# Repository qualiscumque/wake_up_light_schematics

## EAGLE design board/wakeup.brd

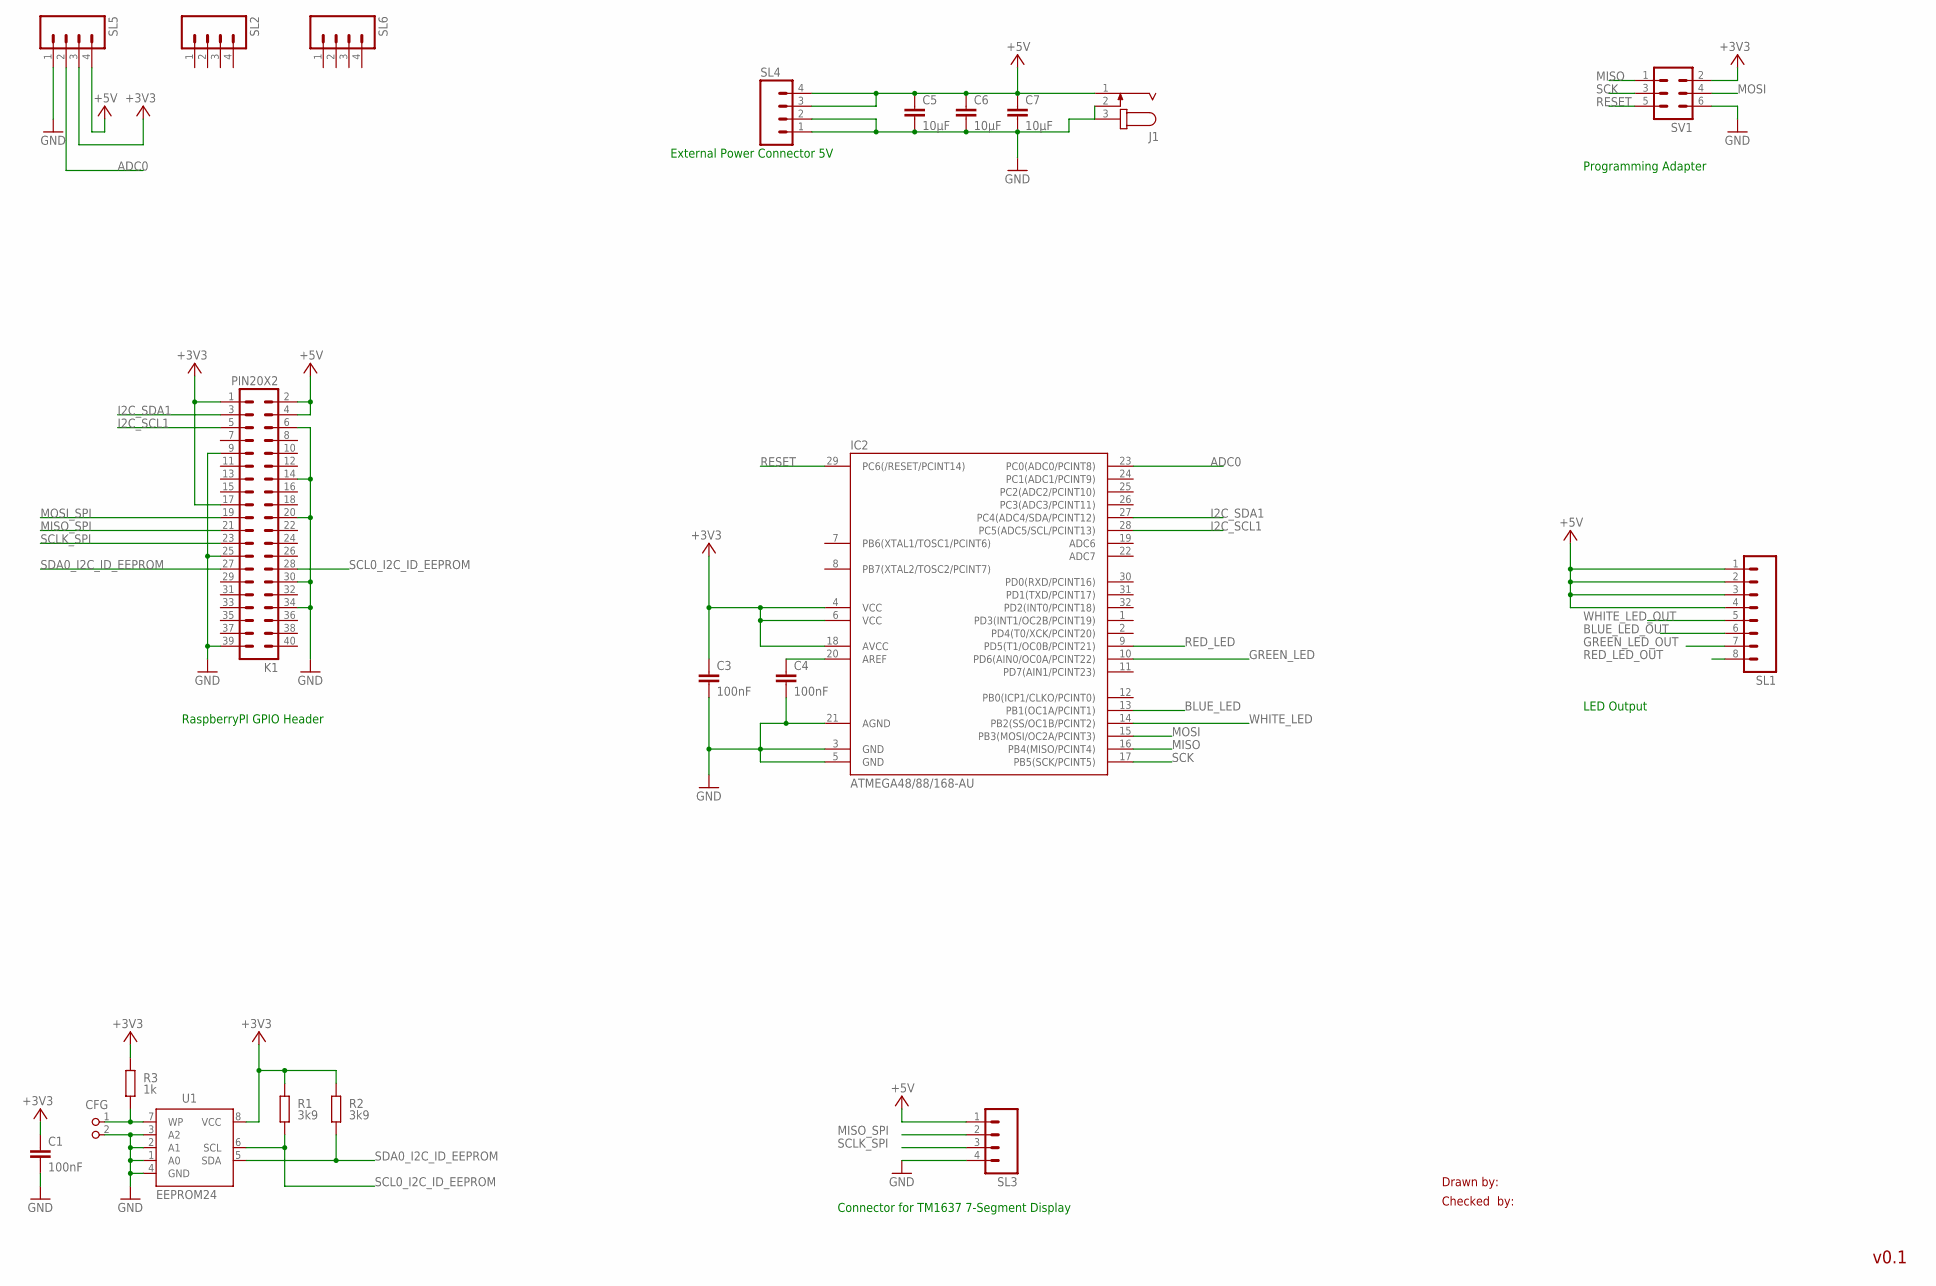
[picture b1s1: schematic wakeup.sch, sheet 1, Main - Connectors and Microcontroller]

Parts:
C1: 100nF; C0805K
C3, C4: 100nF; C0603
C5, C6, C7: 10µF; C0805
CFG: PIN2_100; PIN_W_2
IC2: ATMEGA48/88/168-AU; TQFP32-08
J1: JACK-PLUG1; SPC4078
K1: PIN20X2; PIN_20X2
R1, R2: 3k9; M0805; TOLERANCE 5%
R3: 1k; M0805; TOLERANCE 5%
SL1: M08; 08P
SL2, SL3, SL4, SL5, SL6: M04; 04P
SV1: ML6
U1: EEPROM24; SOIC8

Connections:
+3V3: C1.1, C3.1, IC2.4 (VCC), IC2.6 (VCC), IC2.18 (AVCC), K1.1, K1.17, R1.2, R2.2, R3.2, SL5.3, SV1.2, U1.8 (VCC)
+5V: C5.1, C6.1, C7.1, J1.1, K1.2, K1.4, SL1.1, SL1.2, SL1.3, SL1.4, SL3.1, SL4.3, SL4.4, SL5.4; also elsewhere on the board
ADC0: IC2.23 (PC0(ADC0/PCINT8)), SL5.2
BLUE_LED: IC2.13 (PB1(OC1A/PCINT1)); also elsewhere on the board
BLUE_LED_OUT: SL1.6; also elsewhere on the board
GND: C1.2, C3.2, C4.2, C5.2, C6.2, C7.2, CFG.2, IC2.3 (GND), IC2.5 (GND), IC2.21 (AGND), J1.2, J1.3, K1.6, K1.9, K1.14, K1.20, K1.25, K1.30, K1.34, K1.39, SL3.4, SL4.1, SL4.2, SL5.1, SV1.6, U1.1 (A0), U1.2 (A1), U1.3 (A2), U1.4 (GND); also elsewhere on the board
GREEN_LED: IC2.10 (PD6(AIN0/OC0A/PCINT22)); also elsewhere on the board
GREEN_LED_OUT: SL1.7; also elsewhere on the board
I2C_SCL1: IC2.28 (PC5(ADC5/SCL/PCINT13)), K1.5
I2C_SDA1: IC2.27 (PC4(ADC4/SDA/PCINT12)), K1.3
MISO: IC2.16 (PB4(MISO/PCINT4)), SV1.1
MISO_SPI: K1.21, SL3.2
MOSI: IC2.15 (PB3(MOSI/OC2A/PCINT3)), SV1.4
MOSI_SPI: K1.19
unnamed: CFG.1, R3.1, U1.7 (WP)
unnamed: C4.1, IC2.20 (AREF)
RED_LED: IC2.9 (PD5(T1/OC0B/PCINT21)); also elsewhere on the board
RED_LED_OUT: SL1.8; also elsewhere on the board
RESET: IC2.29 (PC6(/RESET/PCINT14)), SV1.5
SCK: IC2.17 (PB5(SCK/PCINT5)), SV1.3
SCL0_I2C_ID_EEPROM: K1.28, R1.1, U1.6 (SCL)
SCLK_SPI: K1.23, SL3.3
SDA0_I2C_ID_EEPROM: K1.27, R2.1, U1.5 (SDA)
WHITE_LED: IC2.14 (PB2(SS/OC1B/PCINT2)); also elsewhere on the board
WHITE_LED_OUT: SL1.5; also elsewhere on the board

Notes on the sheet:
Drawn by:
Checked by:
v0.1
Connector for TM1637 7-Segment Display
RaspberryPI GPIO Header
External Power Connector 5V
Programming Adapter
LED Output

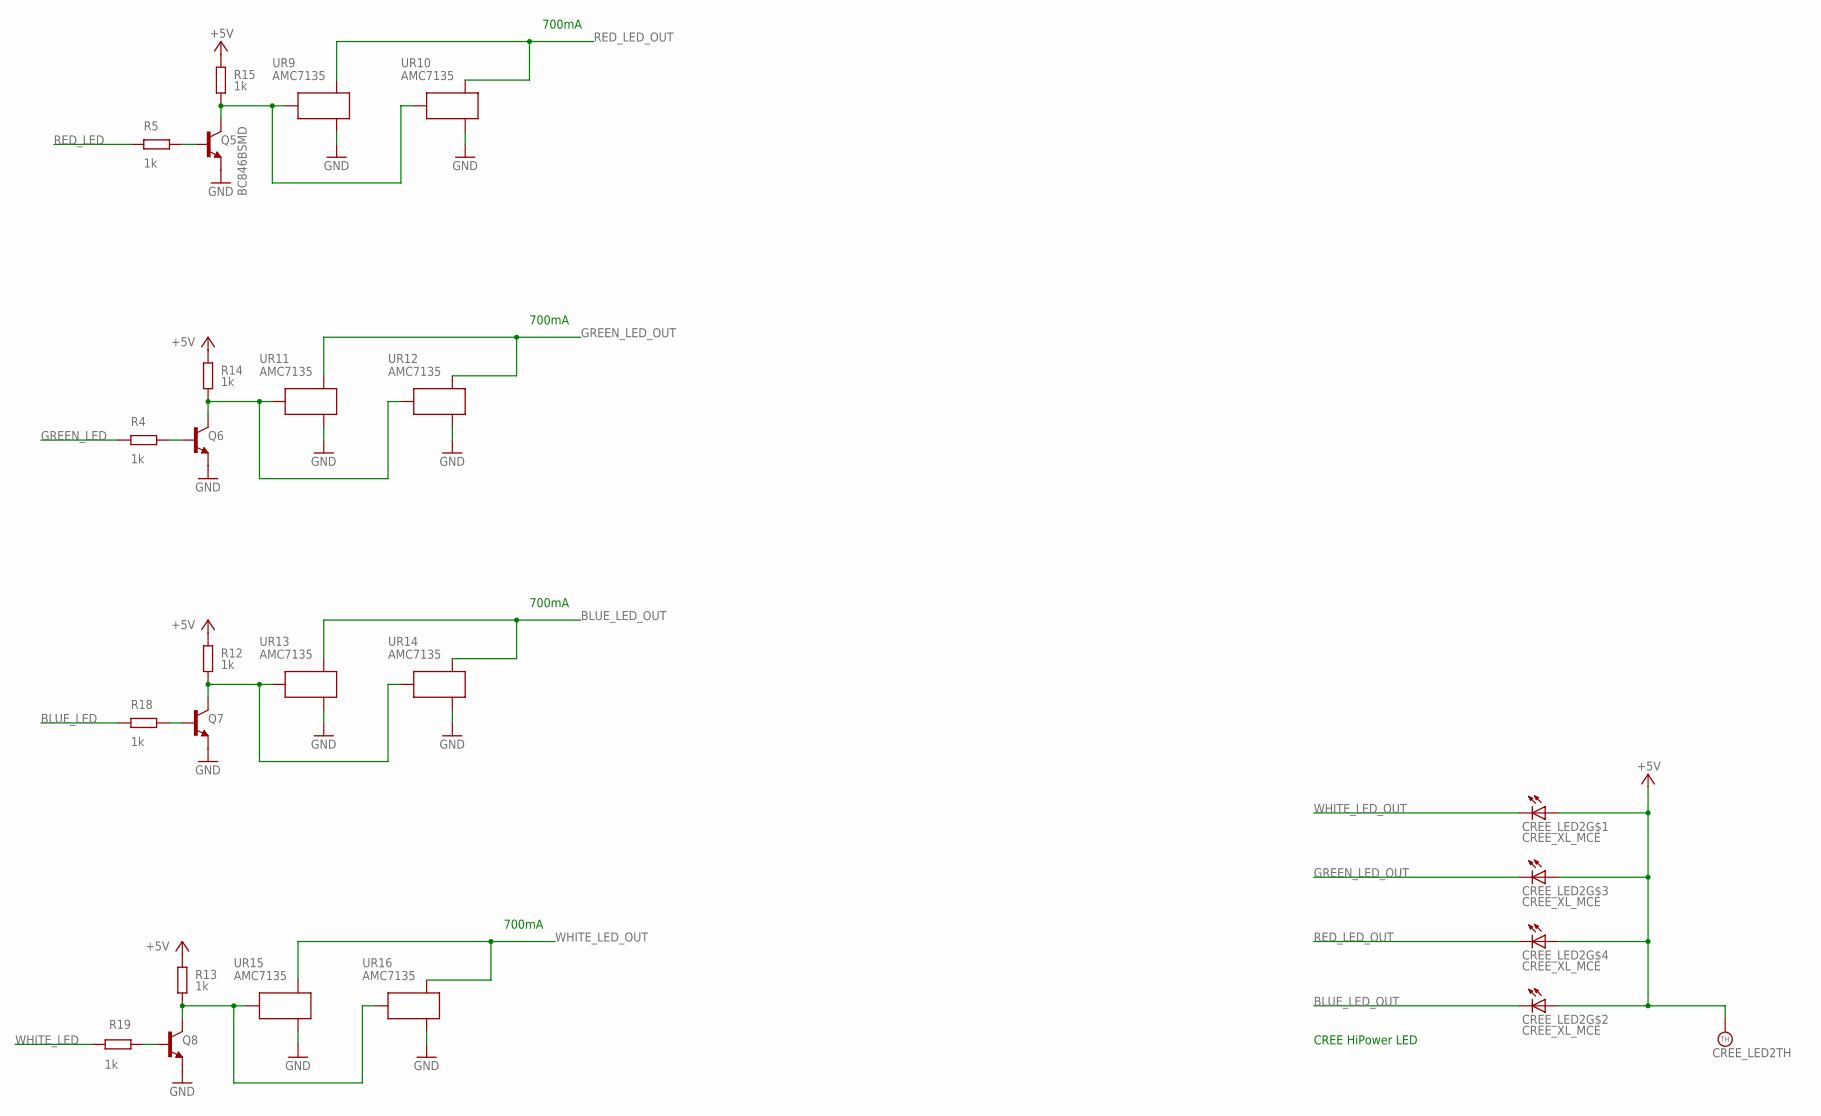
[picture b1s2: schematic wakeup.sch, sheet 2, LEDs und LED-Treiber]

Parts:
CREE_LED2: CREE_XL_MCE
Q5, Q6, Q7, Q8: BC846BSMD; SOT23
R4, R5, R18, R19: 1k; M0805; TOLERANCE 5%
R12, R13, R14, R15: 1k; R0603; TOLERANCE 5%
UR9, UR10, UR11, UR12, UR13, UR14, UR15, UR16: AMC7135; SOT

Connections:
+5V: CREE_LED2.1 (A), CREE_LED2.2 (A), CREE_LED2.3 (A), CREE_LED2.4 (A), CREE_LED2.HT (TH), R12.2, R13.2, R14.2, R15.2; also elsewhere on the board
BLUE_LED: R18.2; also elsewhere on the board
BLUE_LED_OUT: CREE_LED2.7 (C), UR13.1 (OUT), UR14.1 (OUT); also elsewhere on the board
BLUE_POWER: Q7.3 (C), R12.1, UR13.3 (VDD), UR14.3 (VDD)
GND: Q5.2 (E), Q6.2 (E), Q7.2 (E), Q8.2 (E), UR9.2 (GND), UR9.2@1 (GND), UR10.2 (GND), UR10.2@1 (GND), UR11.2 (GND), UR11.2@1 (GND), UR12.2 (GND), UR12.2@1 (GND), UR13.2 (GND), UR13.2@1 (GND), UR14.2 (GND), UR14.2@1 (GND), UR15.2 (GND), UR15.2@1 (GND), UR16.2 (GND), UR16.2@1 (GND); also elsewhere on the board
GREEN_LED: R4.2; also elsewhere on the board
GREEN_LED_OUT: CREE_LED2.6 (C), UR11.1 (OUT), UR12.1 (OUT); also elsewhere on the board
GREEN_POWER: Q6.3 (C), R14.1, UR11.3 (VDD), UR12.3 (VDD)
unnamed: Q8.1 (B), R19.1
unnamed: Q7.1 (B), R18.1
unnamed: Q5.1 (B), R5.1
unnamed: Q6.1 (B), R4.1
RED_LED: R5.2; also elsewhere on the board
RED_LED_OUT: CREE_LED2.5 (C), UR9.1 (OUT), UR10.1 (OUT); also elsewhere on the board
RED_POWER: Q5.3 (C), R15.1, UR9.3 (VDD), UR10.3 (VDD)
WHITE_LED: R19.2; also elsewhere on the board
WHITE_LED_OUT: CREE_LED2.8 (C), UR15.1 (OUT), UR16.1 (OUT); also elsewhere on the board
WHITE_POWER: Q8.3 (C), R13.1, UR15.3 (VDD), UR16.3 (VDD)

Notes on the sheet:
CREE HiPower LED
700mA

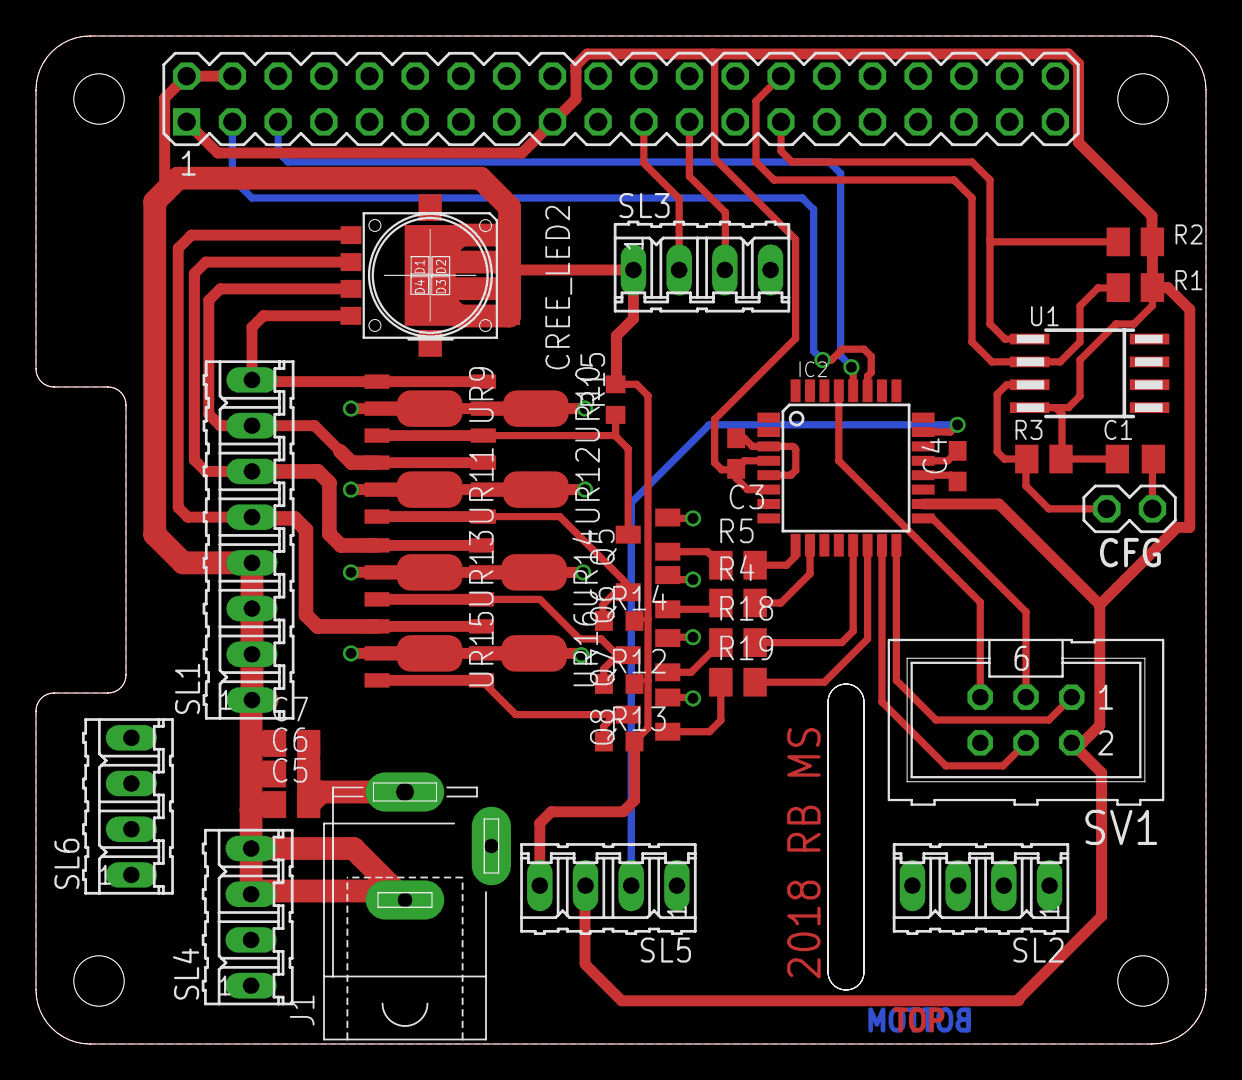
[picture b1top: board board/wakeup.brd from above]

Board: 2 copper layers, 65.0 x 56.0 mm, 42 parts (0 on the bottom side), 32 nets.

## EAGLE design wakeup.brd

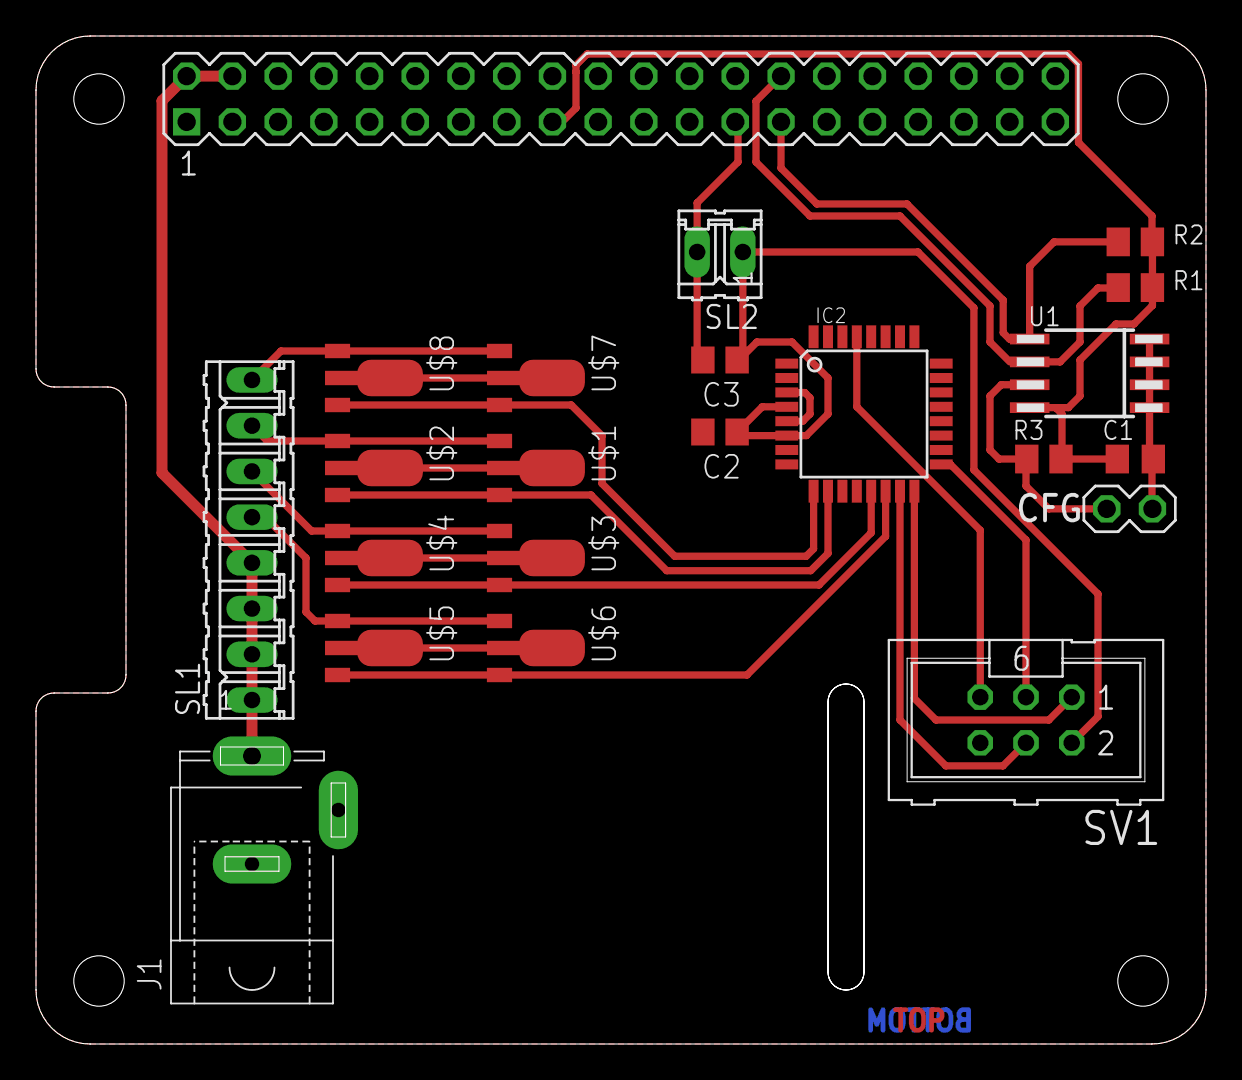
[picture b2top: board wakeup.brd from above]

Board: 2 copper layers, 65.0 x 56.0 mm, 22 parts (0 on the bottom side), 19 nets.

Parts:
C1: 100nF; C0805K
C2, C3: 47nF; C0805
CFG: PIN_W_2
IC2: ATMEGA48/88/168-AU; TQFP32-08
J1: SPC4078
K1: PIN20X2; PIN_20X2
R1, R2: 3k9; M0805
R3: 1k; M0805
SL1: 08P
SL2: 02P
SV1: ML6
U1: EEPROM24; SOIC8
U$1, U$2, U$3, U$4, U$5, U$6, U$7, U$8: AMC7135; SOT

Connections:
+3V3: C1.1, K1.1, K1.17, R1.2, R2.2, R3.2, U1.8
+5V: J1.3, K1.2, K1.4, SL1.1, SL1.2, SL1.3, SL1.4
BLUE_LED: IC2.13, U$3.3, U$4.3
BLUE_LED_OUT: SL1.6, U$3.1, U$4.1
GND: C1.2, C2.2, C3.2, CFG.2, IC2.3, IC2.5, J1.1, J1.2, K1.6, K1.9, K1.14, K1.20, K1.25, K1.30, K1.34, K1.39, SL2.2, SV1.6, U1.1, U1.2, U1.3, U1.4, U$1.2, U$1.2@1, U$2.2, U$2.2@1, U$3.2, U$3.2@1, U$4.2, U$4.2@1, U$5.2, U$5.2@1, U$6.2, U$6.2@1, U$7.2, U$7.2@1, U$8.2, U$8.2@1
GREEN_LED: IC2.10, U$1.3, U$2.3
GREEN_LED_OUT: SL1.7, U$1.1, U$2.1
MISO: IC2.16, SV1.1
MOSI: IC2.15, SV1.4
unnamed: CFG.1, R3.1, U1.7
RED_LED: IC2.9, U$7.3, U$8.3
RED_LED_OUT: SL1.8, U$7.1, U$8.1
RESET: IC2.29, SV1.5
SCK: IC2.17, SV1.3
SCL0_I2C_ID_EEPROM: K1.28, R1.1, U1.6
SDA0_I2C_ID_EEPROM: K1.27, R2.1, U1.5
VCC: C2.1, C3.1, IC2.4, IC2.6, SL2.1, SV1.2
WHITE_LED: IC2.14, U$5.3, U$6.3
WHITE_LED_OUT: SL1.5, U$5.1, U$6.1

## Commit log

2018-03-25 Added RaspberryPi Library
2018-04-21 Updated board and schematics for RaspberryPI
2018-05-05 Added Power connector and named some nets
2018-05-08 Updated layout
2018-05-09 Updated project structure
2018-05-10 Added gerber file
2018-05-11 Added pin header for tm1637 7-Segment display
2018-05-12 Fixed FCC net, added I2C nets
2018-05-12 Updated ratsnest
2018-05-12 Fixed some naming and added tag
2018-05-16 Much better
2018-05-16 Fixed some errors
2018-05-20 Finalized Updates
2018-05-26 Finalized board. Readded CON_JACK
2018-05-26 Updated circuit rendering
